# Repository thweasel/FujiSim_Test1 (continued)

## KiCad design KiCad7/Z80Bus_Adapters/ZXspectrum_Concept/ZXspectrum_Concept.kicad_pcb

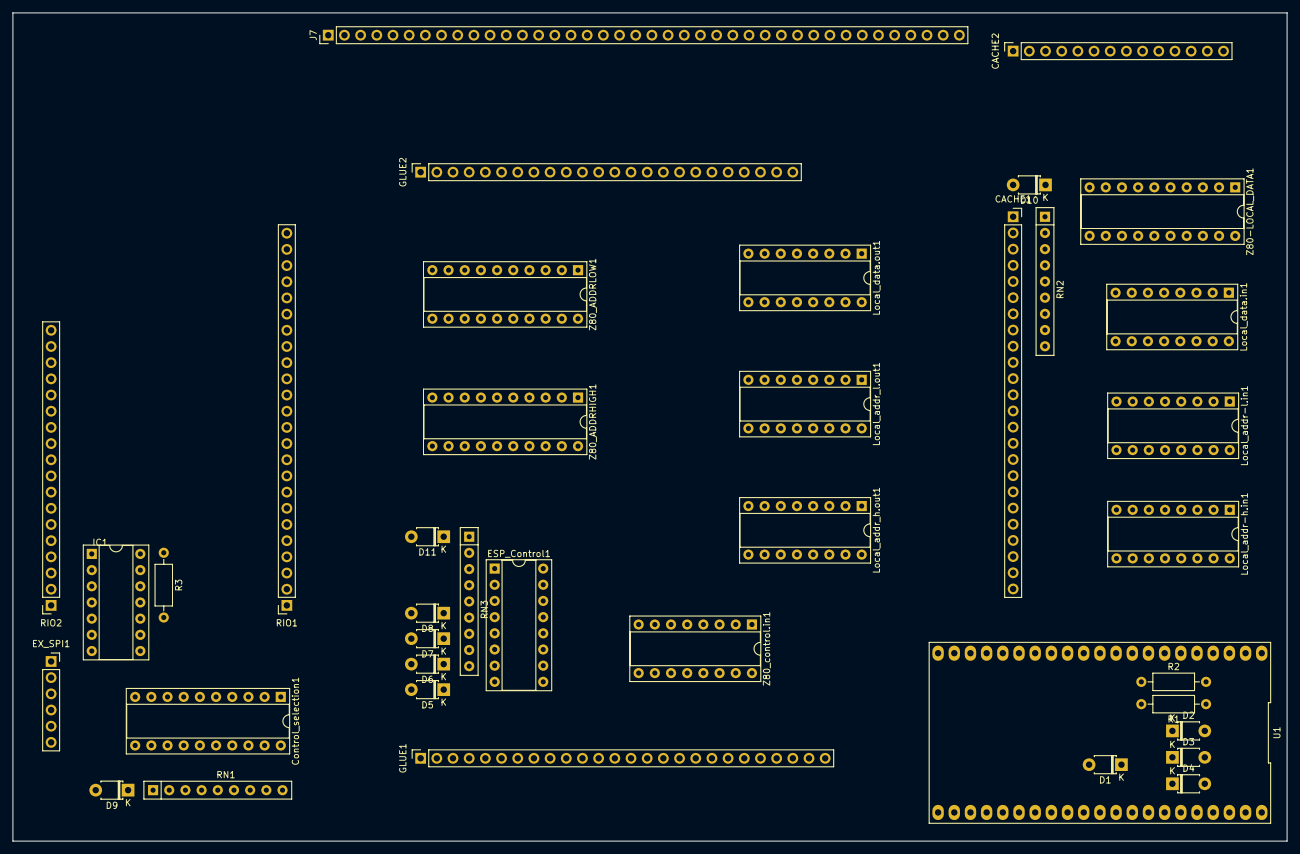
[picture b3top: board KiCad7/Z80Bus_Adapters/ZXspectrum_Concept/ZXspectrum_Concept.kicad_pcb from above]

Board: 2 copper layers, 200.0 x 130.0 mm, 39 parts (0 on the bottom side), 130 nets, no tracks yet.

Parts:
CACHE1: Conn_01x24_Socket; PinSocket_1x24_P2.54mm_Vertical
CACHE2: Conn_01x14_Socket; PinSocket_1x14_P2.54mm_Vertical
Control_selection1: 74HC244N; DIP-20_W7.62mm_Socket
D1, D2, D3, D4, D5, D6, D7, D8, D9, D10, D11: 1N4148; D_T-1_P5.08mm_Horizontal
ESP_Control1: 74595N; DIP-16_W7.62mm_Socket
EX_SPI1: PinSocket_2.54mm; PinSocket_1x06_P2.54mm_Vertical
GLUE1: Conn_01x26_Socket; PinSocket_1x26_P2.54mm_Vertical
GLUE2: Conn_01x24_Socket; PinSocket_1x24_P2.54mm_Vertical
IC1: 74HC32N; DIP-14_W7.62mm_Socket
J7: DIAG-HOST_SYSTEM_BUS; PinHeader_1x40_P2.54mm_Vertical
Local_addr-h.in1: 74HC165N; DIP-16_W7.62mm_Socket
Local_addr-l.in1: 74HC165N; DIP-16_W7.62mm_Socket
Local_addr_h.out1: 74595N; DIP-16_W7.62mm_Socket
Local_addr_l.out1: 74595N; DIP-16_W7.62mm_Socket
Local_data.in1: 74HC165N; DIP-16_W7.62mm_Socket
Local_data.out1: 74595N; DIP-16_W7.62mm_Socket
R1, R2, R3: 22K; R_Axial_DIN0207_L6.3mm_D2.5mm_P10.16mm_Horizontal
RIO1: Conn_01x24_Socket; PinSocket_1x24_P2.54mm_Vertical
RIO2: Conn_01x18_Socket; PinSocket_1x18_P2.54mm_Vertical
RN1: LOCAL_CONTROL_BIAS; R_Array_SIP9
RN2, RN3: 4609M-101-103LF; R_Array_SIP9
U1: FREENOVE_ESP32-WROVER-DEV
Z80-LOCAL_DATA1, Z80_ADDRHIGH1, Z80_ADDRLOW1: 74HC245N; DIP-20_W7.62mm_Socket
Z80_control.in1: 74HC165N; DIP-16_W7.62mm_Socket

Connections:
+5V: CACHE2.1, Control_selection1.20 (VCC), D9.2 (A), D10.2 (A), D11.2 (A), ESP_Control1.16 (VCC), EX_SPI1.5, GLUE1.1, IC1.14 (VCC), Local_addr-h.in1.16 (VCC), Local_addr-l.in1.16 (VCC), Local_addr_h.out1.16 (VCC), Local_addr_l.out1.16 (VCC), Local_data.in1.16 (VCC), Local_data.out1.16 (VCC), R1.2, R3.1, RIO2.1, U1.20 (+5V), Z80-LOCAL_DATA1.20 (VCC), Z80_ADDRHIGH1.20 (VCC), Z80_ADDRLOW1.20 (VCC), Z80_control.in1.16 (VCC)
/CACHE connector/CACHE_CONTROL.A16: CACHE2.2, GLUE2.14
/CACHE connector/CACHE_CONTROL.CS: CACHE2.5, GLUE2.17
/CACHE connector/CACHE_CONTROL.DATASTATUS+PERM_Z80_IORQ: CACHE2.6, GLUE2.13
/CACHE connector/CACHE_CONTROL.OE: CACHE2.4, GLUE2.16
/CACHE connector/CACHE_CONTROL.WE: CACHE2.3, GLUE2.15
/CACHE connector/CACHE_DATASTATUS: CACHE2.12, GLUE2.5, RIO2.13
/CACHE connector/CACHE_SEL_0: CACHE2.8, RIO2.9
/CACHE connector/CACHE_SEL_1: CACHE2.9, RIO2.10
/CACHE connector/CACHE_SEL_2: CACHE2.10, RIO2.11
/CACHE connector/CACHE_SEL_3: CACHE2.11, RIO2.12
/CACHE connector/LOCAL_A0: CACHE1.9, Local_addr-l.in1.11 (D0), Local_addr_l.out1.15 (QA), Z80_ADDRLOW1.18 (B0)
/CACHE connector/LOCAL_A1: CACHE1.10, Local_addr-l.in1.12 (D1), Local_addr_l.out1.1 (QB), Z80_ADDRLOW1.17 (B1)
/CACHE connector/LOCAL_A2: CACHE1.11, Local_addr-l.in1.13 (D2), Local_addr_l.out1.2 (QC), Z80_ADDRLOW1.16 (B2)
/CACHE connector/LOCAL_A3: CACHE1.12, Local_addr-l.in1.14 (D3), Local_addr_l.out1.3 (QD), Z80_ADDRLOW1.15 (B3)
/CACHE connector/LOCAL_A4: CACHE1.13, Local_addr-l.in1.3 (D4), Local_addr_l.out1.4 (QE), Z80_ADDRLOW1.14 (B4)
/CACHE connector/LOCAL_A5: CACHE1.14, Local_addr-l.in1.4 (D5), Local_addr_l.out1.5 (QF), Z80_ADDRLOW1.13 (B5)
/CACHE connector/LOCAL_A6: CACHE1.15, Local_addr-l.in1.5 (D6), Local_addr_l.out1.6 (QG), Z80_ADDRLOW1.12 (B6)
/CACHE connector/LOCAL_A7: CACHE1.16, Local_addr-l.in1.6 (D7), Local_addr_l.out1.7 (QH), Z80_ADDRLOW1.11 (B7)
/CACHE connector/LOCAL_A8: CACHE1.17, Local_addr-h.in1.11 (D0), Local_addr_h.out1.15 (QA), Z80_ADDRHIGH1.18 (B0)
/CACHE connector/LOCAL_A9: CACHE1.18, Local_addr-h.in1.12 (D1), Local_addr_h.out1.1 (QB), Z80_ADDRHIGH1.17 (B1)
/CACHE connector/LOCAL_A10: CACHE1.19, Local_addr-h.in1.13 (D2), Local_addr_h.out1.2 (QC), Z80_ADDRHIGH1.16 (B2)
/CACHE connector/LOCAL_A11: CACHE1.20, Local_addr-h.in1.14 (D3), Local_addr_h.out1.3 (QD), Z80_ADDRHIGH1.15 (B3)
/CACHE connector/LOCAL_A12: CACHE1.21, Local_addr-h.in1.3 (D4), Local_addr_h.out1.4 (QE), Z80_ADDRHIGH1.14 (B4)
/CACHE connector/LOCAL_A13: CACHE1.22, Local_addr-h.in1.4 (D5), Local_addr_h.out1.5 (QF), Z80_ADDRHIGH1.13 (B5)
/CACHE connector/LOCAL_A14: CACHE1.23, Local_addr-h.in1.5 (D6), Local_addr_h.out1.6 (QG), Z80_ADDRHIGH1.12 (B6)
/CACHE connector/LOCAL_A15: CACHE1.24, Local_addr-h.in1.6 (D7), Local_addr_h.out1.7 (QH), Z80_ADDRHIGH1.11 (B7)
/CACHE connector/LOCAL_D0: CACHE1.1, Local_data.in1.11 (D0), Local_data.out1.15 (QA), RN2.2 (R1), Z80-LOCAL_DATA1.18 (B0)
/CACHE connector/LOCAL_D1: CACHE1.2, Local_data.in1.12 (D1), Local_data.out1.1 (QB), RN2.3 (R2), Z80-LOCAL_DATA1.17 (B1)
/CACHE connector/LOCAL_D2: CACHE1.3, Local_data.in1.13 (D2), Local_data.out1.2 (QC), RN2.4 (R3), Z80-LOCAL_DATA1.16 (B2)
/CACHE connector/LOCAL_D3: CACHE1.4, Local_data.in1.14 (D3), Local_data.out1.3 (QD), RN2.5 (R4), Z80-LOCAL_DATA1.15 (B3)
/CACHE connector/LOCAL_D4: CACHE1.5, Local_data.in1.3 (D4), Local_data.out1.4 (QE), RN2.6 (R5), Z80-LOCAL_DATA1.14 (B4)
/CACHE connector/LOCAL_D5: CACHE1.6, Local_data.in1.4 (D5), Local_data.out1.5 (QF), RN2.7 (R6), Z80-LOCAL_DATA1.13 (B5)
/CACHE connector/LOCAL_D6: CACHE1.7, Local_data.in1.5 (D6), Local_data.out1.6 (QG), RN2.8 (R7), Z80-LOCAL_DATA1.12 (B6)
/CACHE connector/LOCAL_D7: CACHE1.8, Local_data.in1.6 (D7), Local_data.out1.7 (QH), RN2.9 (R8), Z80-LOCAL_DATA1.11 (B7)
/CACHE connector/Z80_HARDLOCK: CACHE2.7, GLUE1.22, U1.4 (GPIO39)
/CORE/ESP_HARDLOCK: GLUE1.20, U1.26 (GPIO2)
/CORE/ESP_INT: D2.2 (A), D3.2 (A), D4.2 (A), R1.1, R2.2, U1.3 (GPIO36)
/CORE/ESP_PULSE: IC1.1, U1.11 (GPIO27)
/CORE/ESP_ROMSEL_0: GLUE1.18, U1.23 (GPIO7)
/CORE/ESP_ROMSEL_1: GLUE1.19, U1.22 (GPIO6)
/CORE/ESP_ROM_WR_PROTECT: GLUE1.17, U1.28 (GPIO4)
/CORE/ESP_SPI_INT.CE: Local_addr-h.in1.15 (~CE), Local_addr-l.in1.15 (~CE), Local_data.in1.15 (~CE), U1.31 (GPIO5), Z80_control.in1.15 (~CE)
/CORE/ESP_SPI_INT.MISO: Local_addr-h.in1.7 (~Q7), U1.33 (GPIO19)
/CORE/ESP_SPI_INT.MOSI: Local_data.out1.14 (SER), U1.39 (GPIO23)
/CORE/ESP_SPI_INT.MR: ESP_Control1.10 (~SRCLR), Local_addr_h.out1.10 (~SRCLR), Local_addr_l.out1.10 (~SRCLR), Local_data.out1.10 (~SRCLR), R3.2
/CORE/ESP_SPI_INT.OE: ESP_Control1.13 (~OE), Local_addr_h.out1.13 (~OE), Local_addr_l.out1.13 (~OE), U1.8 (GPIO33)
/CORE/ESP_SPI_INT.PL: Local_addr-h.in1.1 (~PL), Local_addr-l.in1.1 (~PL), Local_data.in1.1 (~PL), U1.9 (GPIO25), Z80_control.in1.1 (~PL)
/CORE/ESP_SPI_INT.SCK: ESP_Control1.11 (SRCLK), Local_addr-h.in1.2 (CP), Local_addr-l.in1.2 (CP), Local_addr_h.out1.11 (SRCLK), Local_addr_l.out1.11 (SRCLK), Local_data.in1.2 (CP), Local_data.out1.11 (SRCLK), U1.32 (GPIO18), Z80_control.in1.2 (CP)
/CORE/ESP_SPI_INT.STC: ESP_Control1.12 (RCLK), Local_addr_h.out1.12 (RCLK), Local_addr_l.out1.12 (RCLK), Local_data.out1.12 (RCLK), U1.10 (GPIO26)
/CORE/ESP_WAIT_RESET: GLUE2.6, U1.18 (GPIO11)
/CORE/EX_MISO: EX_SPI1.3, U1.13 (GPIO12)
/CORE/EX_MOSI: EX_SPI1.4, U1.15 (GPIO13)
/CORE/EX_SCK: EX_SPI1.2, U1.12 (GPIO14)
/CORE/EX_SS: EX_SPI1.1, U1.25 (GPIO8)
/CORE/SD_CARD_SS: U1.24 (GPIO15), U1.38 (GPIO22)
/CORE/Z80_HARDLOCK_RESET: D3.1 (K), GLUE2.3, RIO2.15
/GLUE connector/!ESP_HARDLOCK: Control_selection1.19 (2OE), GLUE1.21
/GLUE connector/PERM_Z80_IORQ: GLUE1.24, RIO2.17
/GLUE connector/RIO_CONTROL.A14: GLUE2.20, RIO2.4
/GLUE connector/RIO_CONTROL.A15: GLUE2.19, RIO2.3
/GLUE connector/RIO_CONTROL.A16: GLUE2.18, RIO2.2
/GLUE connector/RIO_CONTROL.CE: GLUE2.23, RIO2.6
/GLUE connector/RIO_CONTROL.OE: GLUE2.22, RIO2.7
/GLUE connector/RIO_CONTROL.ROM_RDY: GLUE2.24, RIO2.8
/GLUE connector/RIO_CONTROL.WE: GLUE2.21, RIO2.5
/GLUE connector/WAIT_IO: GLUE2.4, RIO2.14
/GLUE connector/Z80_BUS_CONTROL.Z80_ADD_DIR: GLUE2.10, Z80_ADDRHIGH1.1 (A->B), Z80_ADDRLOW1.1 (A->B)
/GLUE connector/Z80_BUS_CONTROL.Z80_ADD_OE: GLUE2.9, Z80_ADDRHIGH1.19 (CE), Z80_ADDRLOW1.19 (CE)
/GLUE connector/Z80_BUS_CONTROL.Z80_DATA_DIR: GLUE2.11, Z80-LOCAL_DATA1.1 (A->B)
/GLUE connector/Z80_BUS_CONTROL.Z80_DATA_OE: GLUE2.12, Z80-LOCAL_DATA1.19 (CE)
/GLUE connector/Z80_HARDLOCK_SET: GLUE2.2, RIO2.16
/RIO connector/Z80_A0: GLUE2.1, J7.18, RIO1.9, Z80_ADDRLOW1.2 (A0)
/RIO connector/Z80_A1: J7.17, RIO1.10, Z80_ADDRLOW1.3 (A1)
/RIO connector/Z80_A2: J7.16, RIO1.11, Z80_ADDRLOW1.4 (A2)
/RIO connector/Z80_A3: J7.15, RIO1.12, Z80_ADDRLOW1.5 (A3)
/RIO connector/Z80_A4: J7.14, RIO1.13, Z80_ADDRLOW1.6 (A4)
/RIO connector/Z80_A5: J7.13, RIO1.14, Z80_ADDRLOW1.7 (A5)
/RIO connector/Z80_A6: J7.12, RIO1.15, Z80_ADDRLOW1.8 (A6)
/RIO connector/Z80_A7: J7.11, RIO1.16, Z80_ADDRLOW1.9 (A7)
/RIO connector/Z80_A8: J7.26, RIO1.17, Z80_ADDRHIGH1.2 (A0)
/RIO connector/Z80_A9: J7.25, RIO1.18, Z80_ADDRHIGH1.3 (A1)
/RIO connector/Z80_A10: J7.24, RIO1.19, Z80_ADDRHIGH1.4 (A2)
/RIO connector/Z80_A11: J7.23, RIO1.20, Z80_ADDRHIGH1.5 (A3)
/RIO connector/Z80_A12: J7.22, RIO1.21, Z80_ADDRHIGH1.6 (A4)
/RIO connector/Z80_A13: J7.21, RIO1.22, Z80_ADDRHIGH1.7 (A5)
/RIO connector/Z80_A14: GLUE2.7, J7.20, RIO1.23, Z80_ADDRHIGH1.8 (A6)
/RIO connector/Z80_A15: GLUE2.8, J7.19, RIO1.24, Z80_ADDRHIGH1.9 (A7)
/RIO connector/Z80_D0: J7.34, RIO1.1, Z80-LOCAL_DATA1.2 (A0)
/RIO connector/Z80_D1: J7.33, RIO1.2, Z80-LOCAL_DATA1.3 (A1)
/RIO connector/Z80_D2: J7.32, RIO1.3, Z80-LOCAL_DATA1.4 (A2)
/RIO connector/Z80_D3: J7.31, RIO1.4, Z80-LOCAL_DATA1.5 (A3)
/RIO connector/Z80_D4: J7.30, RIO1.5, Z80-LOCAL_DATA1.6 (A4)
/RIO connector/Z80_D5: J7.29, RIO1.6, Z80-LOCAL_DATA1.7 (A5)
/RIO connector/Z80_D6: J7.28, RIO1.7, Z80-LOCAL_DATA1.8 (A6)
/RIO connector/Z80_D7: J7.27, RIO1.8, Z80-LOCAL_DATA1.9 (A7)
/SPI/ESP_CONTROL.BUSRQ: Control_selection1.1 (1OE), D8.1 (K), ESP_Control1.4 (QE), GLUE1.15, RN3.6 (R5)
/SPI/ESP_CONTROL.IORQ: Control_selection1.6 (1A2), Control_selection1.13 (2A2), ESP_Control1.2 (QC), GLUE1.13, RN3.4 (R3)
/SPI/ESP_CONTROL.MEMRQ: Control_selection1.8 (1A3), Control_selection1.11 (2A3), ESP_Control1.3 (QD), GLUE1.14, RN3.5 (R4)
/SPI/ESP_CONTROL.NMI: D5.1 (K), ESP_Control1.7 (QH), RN3.9 (R8)
/SPI/ESP_CONTROL.RD: Control_selection1.2 (1A0), Control_selection1.17 (2A0), ESP_Control1.15 (QA), RN3.2 (R1)
/SPI/ESP_CONTROL.ROMCS: D6.1 (K), ESP_Control1.6 (QG), GLUE1.16, RN3.8 (R7)
/SPI/ESP_CONTROL.WAIT: D7.1 (K), ESP_Control1.5 (QF), RN3.7 (R6)
/SPI/ESP_CONTROL.WR: ESP_Control1.1 (QB), GLUE1.12, IC1.2, Local_data.out1.13 (~OE), RN3.3 (R2)
/SPI/ESP_CONTROL.WR+ESP_PULSE: Control_selection1.4 (1A1), Control_selection1.15 (2A1), IC1.3
/SPI/LOCAL_CONTROL.IORQ: Control_selection1.14 (1Y2), GLUE1.10, RN1.3 (R2)
/SPI/LOCAL_CONTROL.MEMRQ: Control_selection1.12 (1Y3), GLUE1.11, RN1.2 (R1)
/SPI/LOCAL_CONTROL.RD: Control_selection1.18 (1Y0), GLUE1.8, RN1.5 (R4)
/SPI/LOCAL_CONTROL.WR: Control_selection1.16 (1Y1), GLUE1.9, RN1.4 (R3)
/SPI/Z80_CONTROL.BUSACK: D4.1 (K), J7.9, Z80_control.in1.5 (D6)
/SPI/Z80_CONTROL.BUSRQ: D8.2 (A), GLUE1.6, J7.5, Z80_control.in1.3 (D4)
/SPI/Z80_CONTROL.IORQ: Control_selection1.7 (2Y2), GLUE1.4, J7.3, Z80_control.in1.13 (D2)
/SPI/Z80_CONTROL.MEMRQ: Control_selection1.9 (2Y3), GLUE1.5, J7.4, Z80_control.in1.14 (D3)
/SPI/Z80_CONTROL.NMI: D5.2 (A), J7.7, Z80_control.in1.6 (D7)
/SPI/Z80_CONTROL.RD: Control_selection1.3 (2Y0), GLUE1.2, J7.1, Z80_control.in1.11 (D0)
/SPI/Z80_CONTROL.RESET: D1.2 (A), J7.10
/SPI/Z80_CONTROL.ROMCS: D6.2 (A), J7.8
/SPI/Z80_CONTROL.WAIT: D2.1 (K), D7.2 (A), GLUE1.7, J7.6, Z80_control.in1.4 (D5)
/SPI/Z80_CONTROL.WR: Control_selection1.5 (2Y1), GLUE1.3, J7.2, Z80_control.in1.12 (D1)
GND: CACHE2.14, Control_selection1.10 (GND), ESP_Control1.8 (GND), EX_SPI1.6, GLUE1.26, IC1.4, IC1.5, IC1.7 (GND), IC1.9, IC1.10, IC1.12, IC1.13, J7.40, Local_addr-h.in1.8 (GND), Local_addr-l.in1.8 (GND), Local_addr_h.out1.8 (GND), Local_addr_l.out1.8 (GND), Local_data.in1.8 (GND), Local_data.in1.10 (DS), Local_data.out1.8 (GND), R2.1, RIO2.18, U1.21 (GND), U1.34 (GND), U1.40 (GND), Z80-LOCAL_DATA1.10 (GND), Z80_ADDRHIGH1.10 (GND), Z80_ADDRLOW1.10 (GND), Z80_control.in1.8 (GND)
unnamed: D1.1 (K), U1.35 (GPIO21)
unnamed: D9.1 (K), RN1.1 (common)
unnamed: D10.1 (K), RN2.1 (common)
unnamed: D11.1 (K), RN3.1 (common)
unnamed: ESP_Control1.9 (QH'), Local_addr_l.out1.14 (SER)
unnamed: ESP_Control1.14 (SER), Local_data.out1.9 (QH')
unnamed: Local_addr-h.in1.10 (DS), Local_addr-l.in1.7 (~Q7)
unnamed: Local_addr-l.in1.10 (DS), Z80_control.in1.7 (~Q7)
unnamed: Local_addr_h.out1.14 (SER), Local_addr_l.out1.9 (QH')
unnamed: Local_data.in1.7 (~Q7), Z80_control.in1.10 (DS)

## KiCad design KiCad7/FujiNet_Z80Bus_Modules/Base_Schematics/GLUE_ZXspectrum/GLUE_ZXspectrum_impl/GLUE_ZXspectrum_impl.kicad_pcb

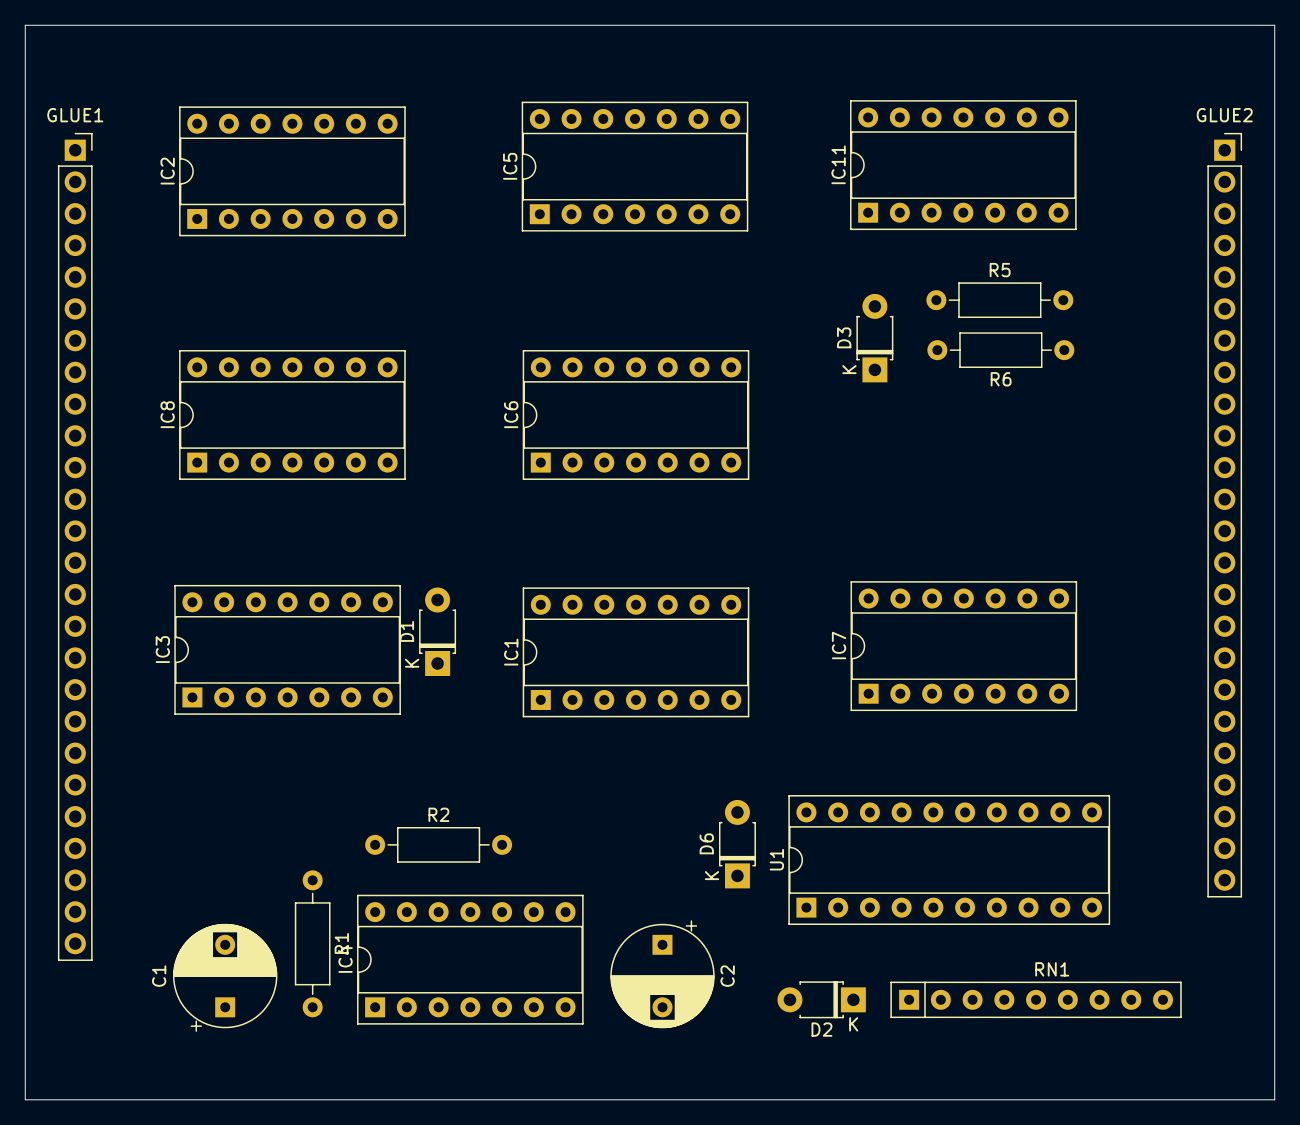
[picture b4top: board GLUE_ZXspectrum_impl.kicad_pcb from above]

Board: 2 copper layers, 100.0 x 86.0 mm, 23 parts (0 on the bottom side), 72 nets, no tracks yet.

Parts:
C1, C2: 10UF; CP_Radial_D8.0mm_P5.00mm
D1, D2, D3, D6: 1N4148; D_T-1_P5.08mm_Horizontal
GLUE1: Conn_01x26_Socket; PinSocket_1x26_P2.54mm_Vertical
GLUE2: Conn_01x24_Socket; PinSocket_1x24_P2.54mm_Vertical
IC1: 7404N; DIP-14_W7.62mm_Socket
IC2, IC5, IC7: 74HC32N; DIP-14_W7.62mm_Socket
IC3: 7474N; DIP-14_W7.62mm_Socket
IC4, IC6, IC8, IC11: 74HC08N; DIP-14_W7.62mm_Socket
R1, R2: 22K; R_Axial_DIN0207_L6.3mm_D2.5mm_P10.16mm_Horizontal
R5, R6: 10K; R_Axial_DIN0207_L6.3mm_D2.5mm_P10.16mm_Horizontal
RN1: 4609M-101-103LF; R_Array_SIP9
U1: 74HC244N; DIP-20_W7.62mm_Socket

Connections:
+5V: D6.2 (A), GLUE1.1, IC1.14 (VCC), IC2.14 (VCC), IC3.14 (VCC), IC4.14 (VCC), IC5.14 (VCC), IC6.14 (VCC), IC7.14 (VCC), IC8.7 (GND), IC11.7 (GND), R1.1, R2.1, R5.2, R6.1, U1.20 (VCC)
/!ESP_HARDLOCK: GLUE1.21, IC1.2
/!Z80_HARDLOCK: GLUE1.23, IC3.6 (~Q)
/CACHE_CONTROL.A16: GLUE2.14, IC8.3
/CACHE_CONTROL.CS: GLUE2.17, IC8.11
/CACHE_CONTROL.DATASTATUS+PERM_Z80_IORQ: GLUE2.13, IC2.6
/CACHE_CONTROL.OE: GLUE2.16, IC8.8
/CACHE_CONTROL.WE: GLUE2.15, IC8.6
/CACHE_DATASTATUS: GLUE2.5, IC1.11, IC2.5, IC8.1
/ESP_CONTROL.BUSRQ: GLUE1.15, IC7.10
/ESP_CONTROL.IORQ: GLUE1.13, IC6.5
/ESP_CONTROL.MEMRQ: GLUE1.14, IC6.4, IC11.4
/ESP_CONTROL.ROMCS: GLUE1.16, IC5.9
/ESP_CONTROL.WR: GLUE1.12, IC5.4
/ESP_HARDLOCK: GLUE1.20, IC1.1, IC2.2, IC2.9
/ESP_ROMSEL_0: GLUE1.18, U1.15 (2A1)
/ESP_ROMSEL_1: GLUE1.19, U1.17 (2A0)
/ESP_ROM_WR_PROTECT: GLUE1.17, IC7.13
/ESP_WAIT_RESET: C2.1, GLUE2.6, IC3.13 (~R), R2.2
/GLUE_ZXspectrum/CLR_Z80_HARDLOCK: IC3.1 (~R), IC4.3
/GLUE_ZXspectrum/ESP_IOD_CONFIG: IC4.5, IC4.12, IC5.1, IC5.13, IC7.8, IC11.5
/GLUE_ZXspectrum/PRE_Z80_HARDLOCK: IC2.3, IC3.4 (~S)
/GLUE_ZXspectrum/RIO CONTROL/ROM_WR_PROTECT+Z80_WR: IC7.11, U1.13 (2A2)
/GLUE_ZXspectrum/RIO CONTROL/Z80_RD+ESP_IOD_CONFIG+PERM_Z80_IORQ: IC6.3, U1.8 (1A3)
/GLUE_ZXspectrum/RIO CONTROL/Z80_WR+ESP_IOD_CONFIG: IC5.3, U1.6 (1A2)
/GLUE_ZXspectrum/Z80 BUS CONTROL/!CACHE_DATASTATUS: IC1.10, IC7.2
/GLUE_ZXspectrum/Z80 BUS CONTROL/Z80_ADD_CONNECT: D2.2 (A), IC11.2, R5.1
/GLUE_ZXspectrum/Z80 BUS CONTROL/Z80_DATA_CONNECT: D3.2 (A), IC5.5, IC11.13, R6.2
/IORQ_FILTER_BIT: GLUE2.1, IC2.12
/LOCAL_CONTROL.IORQ: GLUE1.10, IC8.2
/LOCAL_CONTROL.MEMRQ: GLUE1.11, IC8.13
/LOCAL_CONTROL.RD: GLUE1.8, IC8.10
/LOCAL_CONTROL.WR: GLUE1.9, IC8.5
/PERM_Z80_IORQ: GLUE1.24, IC2.4, IC2.11, IC4.4, IC6.1, IC7.1, IC7.5, IC8.12, IC11.12
/RIO_CONTROL.A14: GLUE2.20, RN1.2 (R1), U1.3 (2Y0), U1.18 (1Y0)
/RIO_CONTROL.A15: GLUE2.19, RN1.3 (R2), U1.5 (2Y1), U1.16 (1Y1)
/RIO_CONTROL.A16: GLUE2.18, IC4.6, IC4.10, U1.1 (1OE)
/RIO_CONTROL.CE: GLUE2.23, IC4.8
/RIO_CONTROL.OE: GLUE2.22, RN1.5 (R4), U1.9 (2Y3), U1.12 (1Y3)
/RIO_CONTROL.ROM_RDY: GLUE2.24, IC4.13, IC5.8, U1.19 (2OE)
/RIO_CONTROL.WE: GLUE2.21, RN1.4 (R3), U1.7 (2Y2), U1.14 (1Y2)
/WAIT_IO: GLUE2.4, IC1.9
/Z80_A14: GLUE2.8, U1.4 (1A1)
/Z80_A15: GLUE2.7, U1.2 (1A0)
/Z80_BUS_CONTROL.Z80_ADD_DIR: GLUE2.10, IC11.6
/Z80_BUS_CONTROL.Z80_ADD_OE: GLUE2.9, IC11.3
/Z80_BUS_CONTROL.Z80_DATA_DIR: GLUE2.11, IC11.8
/Z80_BUS_CONTROL.Z80_DATA_OE: GLUE2.12, IC11.11
/Z80_CONTROL.BUSRQ: D2.1 (K), D3.1 (K), GLUE1.6
/Z80_CONTROL.IORQ: GLUE1.4, IC2.10
/Z80_CONTROL.MEMRQ: GLUE1.5, IC5.10
/Z80_CONTROL.RD: GLUE1.2, IC5.12, IC7.4, IC8.9, U1.11 (2A3)
/Z80_CONTROL.WAIT: D1.2 (A), GLUE1.7
/Z80_CONTROL.WR: GLUE1.3, IC5.2, IC7.12, IC8.4
/Z80_HARDLOCK: GLUE1.22, IC3.5 (Q)
/Z80_HARDLOCK_RESET: GLUE2.2, IC1.5
/Z80_HARDLOCK_SET: GLUE2.3, IC1.3
GND: C1.2, C2.2, GLUE1.26, IC1.7 (GND), IC2.7 (GND), IC3.7 (GND), IC4.7 (GND), IC5.7 (GND), IC6.7 (GND), IC6.9, IC6.10, IC6.12, IC6.13, IC7.7 (GND), IC8.14 (VCC), IC11.14 (VCC), U1.10 (GND)
unnamed: C1.1, IC4.1, R1.2
unnamed: D1.1 (K), IC3.8 (~Q)
unnamed: D6.1 (K), RN1.1 (common)
unnamed: IC1.4, IC2.1
unnamed: IC1.6, IC4.2
unnamed: IC1.12, IC7.9
unnamed: IC1.13, IC6.6
unnamed: IC2.8, IC2.13
unnamed: IC1.8, IC3.10 (~S)
unnamed: IC4.9, IC4.11
unnamed: IC5.11, IC6.2
unnamed: IC7.3, IC11.1
unnamed: IC5.6, IC11.9
unnamed: IC7.6, IC11.10

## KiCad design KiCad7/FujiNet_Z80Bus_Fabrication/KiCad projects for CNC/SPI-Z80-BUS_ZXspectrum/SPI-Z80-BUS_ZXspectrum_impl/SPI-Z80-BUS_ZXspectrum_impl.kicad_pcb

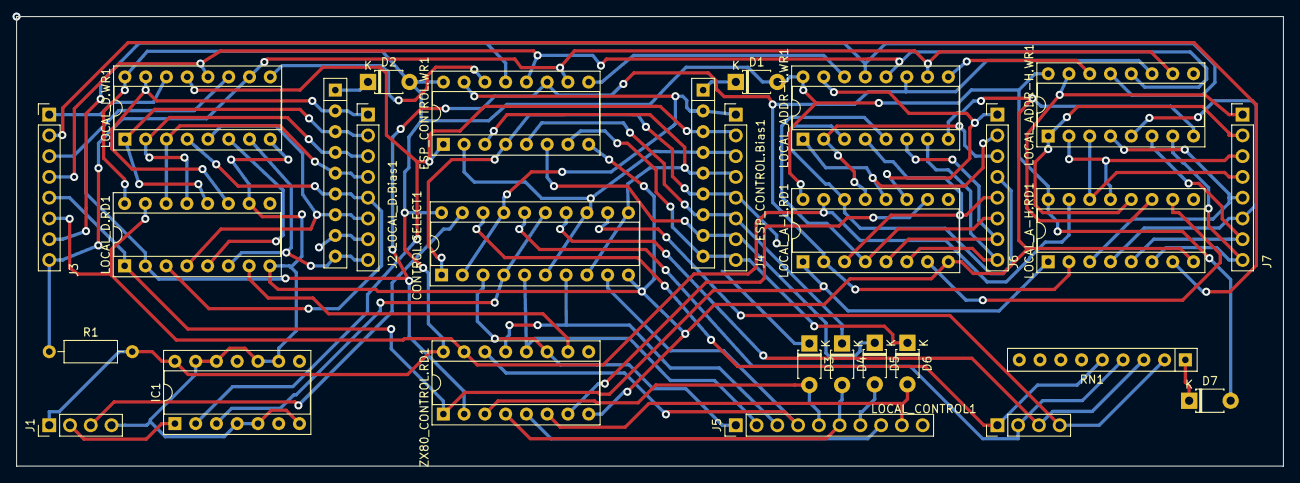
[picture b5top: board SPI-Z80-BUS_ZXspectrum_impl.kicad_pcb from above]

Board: 2 copper layers, 155.0 x 55.0 mm, 29 parts (0 on the bottom side), 67 nets.

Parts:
CONTROL.SELECT1: 74HC244N; DIP-20_W7.62mm_Socket
D1, D2, D3, D4, D5, D6, D7: 1N4148; D_T-1_P5.08mm_Horizontal
ESP_CONTROL.Bias1: 4609M-101-103LF; R_Array_SIP9
ESP_CONTROL.WR1: 74595N; DIP-16_W7.62mm_Socket
IC1: 74HC32N; DIP-14_W7.62mm_Socket
J1: PinHeader_2.54mm; PinHeader_1x04_P2.54mm_Vertical
J2: LOCAL_D; PinHeader_1x08_P2.54mm_Vertical
J3: ESP_SPI_INT; PinHeader_1x08_P2.54mm_Vertical
J4: ESP_CONTROL; PinHeader_1x08_P2.54mm_Vertical
J5: Z80_CONTROL; PinHeader_1x10_P2.54mm_Vertical
J6: LOCAL_A-L; PinHeader_1x08_P2.54mm_Vertical
J7: LOCAL_A-H; PinHeader_1x08_P2.54mm_Vertical
LOCAL_A-H.RD1: 74HC165N; DIP-16_W7.62mm_Socket
LOCAL_A-L.RD1: 74HC165N; DIP-16_W7.62mm_Socket
LOCAL_ADDR-H.WR1: 74595N; DIP-16_W7.62mm_Socket
LOCAL_ADDR-L.WR1: 74595N; DIP-16_W7.62mm_Socket
LOCAL_CONTROL1: LOCAL_CONTROL; PinHeader_1x04_P2.54mm_Vertical
LOCAL_D.Bias1: 4609M-101-103LF; R_Array_SIP9
LOCAL_D.RD1: 74HC165N; DIP-16_W7.62mm_Socket
LOCAL_D.WR1: 74595N; DIP-16_W7.62mm_Socket
R1: 22K; R_Axial_DIN0207_L6.3mm_D2.5mm_P10.16mm_Horizontal
RN1: LOCAL_CONTROL.Bias; R_Array_SIP9
ZX80_CONTROL.RD1: 74HC165N; DIP-16_W7.62mm_Socket

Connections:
+5V: CONTROL.SELECT1.20 (VCC), D1.2 (A), D2.2 (A), D7.2 (A), ESP_CONTROL.WR1.16 (VCC), IC1.14 (VCC), J1.1, LOCAL_A-H.RD1.16 (VCC), LOCAL_A-L.RD1.16 (VCC), LOCAL_ADDR-H.WR1.16 (VCC), LOCAL_ADDR-L.WR1.16 (VCC), LOCAL_D.RD1.16 (VCC), LOCAL_D.WR1.16 (VCC), R1.2, ZX80_CONTROL.RD1.16 (VCC)
/SPI-Z80-BUS/!ESP_HARDLOCK: CONTROL.SELECT1.19 (2OE), J1.3
/SPI-Z80-BUS/ESP_CONTROL.BUSRQ: CONTROL.SELECT1.1 (1OE), D3.1 (K), ESP_CONTROL.Bias1.6 (R5), ESP_CONTROL.WR1.4 (QE), J4.5
/SPI-Z80-BUS/ESP_CONTROL.IORQ: CONTROL.SELECT1.6 (1A2), CONTROL.SELECT1.13 (2A2), ESP_CONTROL.Bias1.4 (R3), ESP_CONTROL.WR1.2 (QC), J4.3
/SPI-Z80-BUS/ESP_CONTROL.MEMRQ: CONTROL.SELECT1.8 (1A3), CONTROL.SELECT1.11 (2A3), ESP_CONTROL.Bias1.5 (R4), ESP_CONTROL.WR1.3 (QD), J4.4
/SPI-Z80-BUS/ESP_CONTROL.NMI: D6.1 (K), ESP_CONTROL.Bias1.9 (R8), ESP_CONTROL.WR1.7 (QH), J4.8
/SPI-Z80-BUS/ESP_CONTROL.RD: CONTROL.SELECT1.2 (1A0), CONTROL.SELECT1.17 (2A0), ESP_CONTROL.Bias1.2 (R1), ESP_CONTROL.WR1.15 (QA), J4.1
/SPI-Z80-BUS/ESP_CONTROL.ROMCS: D5.1 (K), ESP_CONTROL.Bias1.8 (R7), ESP_CONTROL.WR1.6 (QG), J4.7
/SPI-Z80-BUS/ESP_CONTROL.WAIT: D4.1 (K), ESP_CONTROL.Bias1.7 (R6), ESP_CONTROL.WR1.5 (QF), J4.6
/SPI-Z80-BUS/ESP_CONTROL.WR: ESP_CONTROL.Bias1.3 (R2), ESP_CONTROL.WR1.1 (QB), IC1.2, J4.2, LOCAL_D.WR1.13 (~OE)
/SPI-Z80-BUS/ESP_PULSE: IC1.1, J1.2
/SPI-Z80-BUS/ESP_SPI_INT.CE: J3.6, LOCAL_A-H.RD1.15 (~CE), LOCAL_A-L.RD1.15 (~CE), LOCAL_D.RD1.15 (~CE), ZX80_CONTROL.RD1.15 (~CE)
/SPI-Z80-BUS/ESP_SPI_INT.MISO: J3.2, LOCAL_A-H.RD1.7 (~Q7)
/SPI-Z80-BUS/ESP_SPI_INT.MOSI: J3.1, LOCAL_D.WR1.14 (SER)
/SPI-Z80-BUS/ESP_SPI_INT.MR: ESP_CONTROL.WR1.10 (~SRCLR), J3.8, LOCAL_ADDR-H.WR1.10 (~SRCLR), LOCAL_ADDR-L.WR1.10 (~SRCLR), LOCAL_D.WR1.10 (~SRCLR), R1.1
/SPI-Z80-BUS/ESP_SPI_INT.OE: ESP_CONTROL.WR1.13 (~OE), J3.7, LOCAL_ADDR-H.WR1.13 (~OE), LOCAL_ADDR-L.WR1.13 (~OE)
/SPI-Z80-BUS/ESP_SPI_INT.PL: J3.5, LOCAL_A-H.RD1.1 (~PL), LOCAL_A-L.RD1.1 (~PL), LOCAL_D.RD1.1 (~PL), ZX80_CONTROL.RD1.1 (~PL)
/SPI-Z80-BUS/ESP_SPI_INT.SCK: ESP_CONTROL.WR1.11 (SRCLK), J3.3, LOCAL_A-H.RD1.2 (CP), LOCAL_A-L.RD1.2 (CP), LOCAL_ADDR-H.WR1.11 (SRCLK), LOCAL_ADDR-L.WR1.11 (SRCLK), LOCAL_D.RD1.2 (CP), LOCAL_D.WR1.11 (SRCLK), ZX80_CONTROL.RD1.2 (CP)
/SPI-Z80-BUS/ESP_SPI_INT.STC: ESP_CONTROL.WR1.12 (RCLK), J3.4, LOCAL_ADDR-H.WR1.12 (RCLK), LOCAL_ADDR-L.WR1.12 (RCLK), LOCAL_D.WR1.12 (RCLK)
/SPI-Z80-BUS/LOCAL_A0: J6.1, LOCAL_A-L.RD1.11 (D0), LOCAL_ADDR-L.WR1.15 (QA)
/SPI-Z80-BUS/LOCAL_A1: J6.2, LOCAL_A-L.RD1.12 (D1), LOCAL_ADDR-L.WR1.1 (QB)
/SPI-Z80-BUS/LOCAL_A2: J6.3, LOCAL_A-L.RD1.13 (D2), LOCAL_ADDR-L.WR1.2 (QC)
/SPI-Z80-BUS/LOCAL_A3: J6.4, LOCAL_A-L.RD1.14 (D3), LOCAL_ADDR-L.WR1.3 (QD)
/SPI-Z80-BUS/LOCAL_A4: J6.5, LOCAL_A-L.RD1.3 (D4), LOCAL_ADDR-L.WR1.4 (QE)
/SPI-Z80-BUS/LOCAL_A5: J6.6, LOCAL_A-L.RD1.4 (D5), LOCAL_ADDR-L.WR1.5 (QF)
/SPI-Z80-BUS/LOCAL_A6: J6.7, LOCAL_A-L.RD1.5 (D6), LOCAL_ADDR-L.WR1.6 (QG)
/SPI-Z80-BUS/LOCAL_A7: J6.8, LOCAL_A-L.RD1.6 (D7), LOCAL_ADDR-L.WR1.7 (QH)
/SPI-Z80-BUS/LOCAL_A8: J7.1, LOCAL_A-H.RD1.11 (D0), LOCAL_ADDR-H.WR1.15 (QA)
/SPI-Z80-BUS/LOCAL_A9: J7.2, LOCAL_A-H.RD1.12 (D1), LOCAL_ADDR-H.WR1.1 (QB)
/SPI-Z80-BUS/LOCAL_A10: J7.3, LOCAL_A-H.RD1.13 (D2), LOCAL_ADDR-H.WR1.2 (QC)
/SPI-Z80-BUS/LOCAL_A11: J7.4, LOCAL_A-H.RD1.14 (D3), LOCAL_ADDR-H.WR1.3 (QD)
/SPI-Z80-BUS/LOCAL_A12: J7.5, LOCAL_A-H.RD1.3 (D4), LOCAL_ADDR-H.WR1.4 (QE)
/SPI-Z80-BUS/LOCAL_A13: J7.6, LOCAL_A-H.RD1.4 (D5), LOCAL_ADDR-H.WR1.5 (QF)
/SPI-Z80-BUS/LOCAL_A14: J7.7, LOCAL_A-H.RD1.5 (D6), LOCAL_ADDR-H.WR1.6 (QG)
/SPI-Z80-BUS/LOCAL_A15: J7.8, LOCAL_A-H.RD1.6 (D7), LOCAL_ADDR-H.WR1.7 (QH)
/SPI-Z80-BUS/LOCAL_CONTROL.IORQ: CONTROL.SELECT1.14 (1Y2), LOCAL_CONTROL1.3, RN1.3 (R2)
/SPI-Z80-BUS/LOCAL_CONTROL.MEMRQ: CONTROL.SELECT1.12 (1Y3), LOCAL_CONTROL1.4, RN1.2 (R1)
/SPI-Z80-BUS/LOCAL_CONTROL.RD: CONTROL.SELECT1.18 (1Y0), LOCAL_CONTROL1.1, RN1.5 (R4)
/SPI-Z80-BUS/LOCAL_CONTROL.WR: CONTROL.SELECT1.16 (1Y1), LOCAL_CONTROL1.2, RN1.4 (R3)
/SPI-Z80-BUS/LOCAL_D0: J2.1, LOCAL_D.Bias1.2 (R1), LOCAL_D.RD1.11 (D0), LOCAL_D.WR1.15 (QA)
/SPI-Z80-BUS/LOCAL_D1: J2.2, LOCAL_D.Bias1.3 (R2), LOCAL_D.RD1.12 (D1), LOCAL_D.WR1.1 (QB)
/SPI-Z80-BUS/LOCAL_D2: J2.3, LOCAL_D.Bias1.4 (R3), LOCAL_D.RD1.13 (D2), LOCAL_D.WR1.2 (QC)
/SPI-Z80-BUS/LOCAL_D3: J2.4, LOCAL_D.Bias1.5 (R4), LOCAL_D.RD1.14 (D3), LOCAL_D.WR1.3 (QD)
/SPI-Z80-BUS/LOCAL_D4: J2.5, LOCAL_D.Bias1.6 (R5), LOCAL_D.RD1.3 (D4), LOCAL_D.WR1.4 (QE)
/SPI-Z80-BUS/LOCAL_D5: J2.6, LOCAL_D.Bias1.7 (R6), LOCAL_D.RD1.4 (D5), LOCAL_D.WR1.5 (QF)
/SPI-Z80-BUS/LOCAL_D6: J2.7, LOCAL_D.Bias1.8 (R7), LOCAL_D.RD1.5 (D6), LOCAL_D.WR1.6 (QG)
/SPI-Z80-BUS/LOCAL_D7: J2.8, LOCAL_D.Bias1.9 (R8), LOCAL_D.RD1.6 (D7), LOCAL_D.WR1.7 (QH)
/SPI-Z80-BUS/Z80_CONTROL.BUSACK: J5.8, ZX80_CONTROL.RD1.5 (D6)
/SPI-Z80-BUS/Z80_CONTROL.BUSRQ: D3.2 (A), J5.5, ZX80_CONTROL.RD1.3 (D4)
/SPI-Z80-BUS/Z80_CONTROL.IORQ: CONTROL.SELECT1.7 (2Y2), J5.3, ZX80_CONTROL.RD1.13 (D2)
/SPI-Z80-BUS/Z80_CONTROL.MEMRQ: CONTROL.SELECT1.9 (2Y3), J5.4, ZX80_CONTROL.RD1.14 (D3)
/SPI-Z80-BUS/Z80_CONTROL.NMI: D6.2 (A), J5.9, ZX80_CONTROL.RD1.6 (D7)
/SPI-Z80-BUS/Z80_CONTROL.RD: CONTROL.SELECT1.3 (2Y0), J5.1, ZX80_CONTROL.RD1.11 (D0)
/SPI-Z80-BUS/Z80_CONTROL.ROMCS: D5.2 (A), J5.7
/SPI-Z80-BUS/Z80_CONTROL.WAIT: D4.2 (A), J5.6, ZX80_CONTROL.RD1.4 (D5)
/SPI-Z80-BUS/Z80_CONTROL.WR: CONTROL.SELECT1.5 (2Y1), J5.2, ZX80_CONTROL.RD1.12 (D1)
GND: CONTROL.SELECT1.10 (GND), ESP_CONTROL.WR1.8 (GND), IC1.4, IC1.5, IC1.7 (GND), IC1.9, IC1.10, IC1.12, IC1.13, J1.4, LOCAL_A-H.RD1.8 (GND), LOCAL_A-L.RD1.8 (GND), LOCAL_ADDR-H.WR1.8 (GND), LOCAL_ADDR-L.WR1.8 (GND), LOCAL_D.RD1.8 (GND), LOCAL_D.RD1.10 (DS), LOCAL_D.WR1.8 (GND), ZX80_CONTROL.RD1.8 (GND)
unnamed: CONTROL.SELECT1.4 (1A1), CONTROL.SELECT1.15 (2A1), IC1.3
unnamed: D1.1 (K), ESP_CONTROL.Bias1.1 (common)
unnamed: D2.1 (K), LOCAL_D.Bias1.1 (common)
unnamed: D7.1 (K), RN1.1 (common)
unnamed: ESP_CONTROL.WR1.9 (QH'), LOCAL_ADDR-L.WR1.14 (SER)
unnamed: ESP_CONTROL.WR1.14 (SER), LOCAL_D.WR1.9 (QH')
unnamed: LOCAL_A-H.RD1.10 (DS), LOCAL_A-L.RD1.7 (~Q7)
unnamed: LOCAL_A-L.RD1.10 (DS), ZX80_CONTROL.RD1.7 (~Q7)
unnamed: LOCAL_ADDR-H.WR1.14 (SER), LOCAL_ADDR-L.WR1.9 (QH')
unnamed: LOCAL_D.RD1.7 (~Q7), ZX80_CONTROL.RD1.10 (DS)

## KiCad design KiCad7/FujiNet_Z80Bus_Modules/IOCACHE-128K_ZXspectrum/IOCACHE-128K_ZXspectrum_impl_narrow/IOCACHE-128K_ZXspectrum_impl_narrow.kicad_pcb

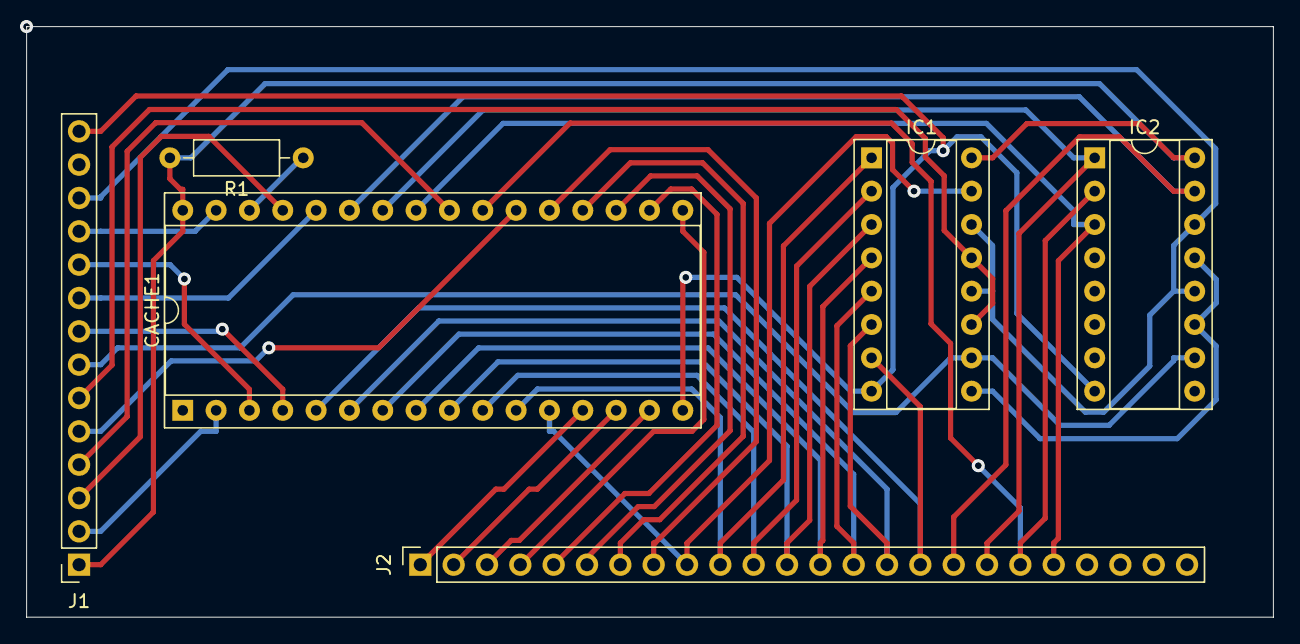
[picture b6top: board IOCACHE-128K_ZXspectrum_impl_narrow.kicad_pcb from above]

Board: 2 copper layers, 95.0 x 45.0 mm, 6 parts (0 on the bottom side), 35 nets.

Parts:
CACHE1: AS6C1008-55PCN; DIP-32_W15.24mm_Socket
IC1, IC2: 74HC590N; DIP-16_W7.62mm_Socket
J1: Conn_01x14_Socket; PinSocket_1x14_P2.54mm_Vertical
J2: Conn_01x24_Socket; PinSocket_1x24_P2.54mm_Vertical
R1: 10K; R_Axial_DIN0207_L6.3mm_D2.5mm_P10.16mm_Horizontal

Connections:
+5V: CACHE1.32 (VCC), IC1.16 (VCC), IC2.16 (VCC), J1.1, R1.2
/IOCACHE-128K_ZXspectrum/CACHE_CE2: CACHE1.30 (CE2#), R1.1
/IOCACHE-128K_ZXspectrum/CACHE_CONTROL.A16: CACHE1.2 (A16), J1.2
/IOCACHE-128K_ZXspectrum/CACHE_CONTROL.CS: CACHE1.22 (CE#), J1.5
/IOCACHE-128K_ZXspectrum/CACHE_CONTROL.DATASTATUS+PERM_Z80_IORQ: IC1.11 (CPC), IC1.13 (CPR), J1.6
/IOCACHE-128K_ZXspectrum/CACHE_CONTROL.OE: CACHE1.24 (OE#), J1.4
/IOCACHE-128K_ZXspectrum/CACHE_CONTROL.WE: CACHE1.29 (WE#), J1.3
/IOCACHE-128K_ZXspectrum/CACHE_DATASTATUS: IC1.12 (~CE), IC1.14 (~OE), IC2.12 (~CE), IC2.14 (~OE), J1.12
/IOCACHE-128K_ZXspectrum/CACHE_SEL_0: CACHE1.4 (A12), J1.8
/IOCACHE-128K_ZXspectrum/CACHE_SEL_1: CACHE1.28 (A13), J1.9
/IOCACHE-128K_ZXspectrum/CACHE_SEL_2: CACHE1.3 (A14), J1.10
/IOCACHE-128K_ZXspectrum/CACHE_SEL_3: CACHE1.31 (A15), J1.11
/IOCACHE-128K_ZXspectrum/LOCAL_A0: CACHE1.12 (A0), IC1.15 (Q0), J2.9
/IOCACHE-128K_ZXspectrum/LOCAL_A1: CACHE1.11 (A1), IC1.1 (Q1), J2.10
/IOCACHE-128K_ZXspectrum/LOCAL_A2: CACHE1.10 (A2), IC1.2 (Q2), J2.11
/IOCACHE-128K_ZXspectrum/LOCAL_A3: CACHE1.9 (A3), IC1.3 (Q3), J2.12
/IOCACHE-128K_ZXspectrum/LOCAL_A4: CACHE1.8 (A4), IC1.4 (Q4), J2.13
/IOCACHE-128K_ZXspectrum/LOCAL_A5: CACHE1.7 (A5), IC1.5 (Q5), J2.14
/IOCACHE-128K_ZXspectrum/LOCAL_A6: CACHE1.6 (A6), IC1.6 (Q6), J2.15
/IOCACHE-128K_ZXspectrum/LOCAL_A7: CACHE1.5 (A7), IC1.7 (Q7), J2.16
/IOCACHE-128K_ZXspectrum/LOCAL_A8: CACHE1.27 (A8), IC2.15 (Q0), J2.17
/IOCACHE-128K_ZXspectrum/LOCAL_A9: CACHE1.26 (A9), IC2.1 (Q1), J2.18
/IOCACHE-128K_ZXspectrum/LOCAL_A10: CACHE1.23 (A10), IC2.2 (Q2), J2.19
/IOCACHE-128K_ZXspectrum/LOCAL_A11: CACHE1.25 (A11), IC2.3 (Q3), J2.20
/IOCACHE-128K_ZXspectrum/LOCAL_D0: CACHE1.13 (DQ0), J2.1
/IOCACHE-128K_ZXspectrum/LOCAL_D1: CACHE1.14 (DQ1), J2.2
/IOCACHE-128K_ZXspectrum/LOCAL_D2: CACHE1.15 (DQ2), J2.3
/IOCACHE-128K_ZXspectrum/LOCAL_D3: CACHE1.17 (DQ3), J2.4
/IOCACHE-128K_ZXspectrum/LOCAL_D4: CACHE1.18 (DQ4), J2.5
/IOCACHE-128K_ZXspectrum/LOCAL_D5: CACHE1.19 (DQ5), J2.6
/IOCACHE-128K_ZXspectrum/LOCAL_D6: CACHE1.20 (DQ6), J2.7
/IOCACHE-128K_ZXspectrum/LOCAL_D7: CACHE1.21 (DQ7), J2.8
/IOCACHE-128K_ZXspectrum/Z80_HARDLOCK: IC1.10 (~MRC), IC2.10 (~MRC), J1.7
GND: CACHE1.16 (VSS), IC1.8 (GND), IC2.8 (GND), J1.14
unnamed: IC1.9 (~RCO), IC2.11 (CPC), IC2.13 (CPR)
